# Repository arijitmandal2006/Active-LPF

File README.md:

**Active Low-Pass Filter (Sallen--Key) Using TLV9061**
=====================================================

### *Designed by Arijit Mandal*

This repository contains the full KiCad project, schematic, PCB design, and supporting documentation for a **2nd-order active low-pass filter** based on the **TLV9061** high-performance CMOS op-amp.\
The filter is implemented in a **unity-gain Sallen--Key topology**, optimized for clean analog signal conditioning.

* * * * *

📘 **Project Overview**
-----------------------

This project implements a precision **Active Low Pass Filter (LPF)** suitable for:

-   Sensor signal conditioning

-   Noise filtering in embedded electronics

-   General analog experimentation

The LPF is centered around the **TLV9061**, a modern rail-to-rail, low-noise, high-bandwidth CMOS operational amplifier from Texas Instruments.

A complete KiCad schematic is shown in **page 1 of the submitted schematic PDF**
**Filter Characteristics**
--------------------------

-   **Topology:**  2nd Order

-   **Configuration:** Unity-gain

-   **Cutoff Frequency (fc):** ~1 kHz (based on selected RC values)

-   **Supply Options:**

    -   **Single-Supply:** +5 V

    -   **Dual-Supply:** +5 V / --5 V

-   **Input Type:** Single-ended AC input

-   **Output Type:** Buffered, low-impedance analog output

* * * * *

📐 **Circuit Diagram**
----------------------
The circuit schematic includes:

-   A AC test source

-   RC network (R1, R2, C1, C2) 

-   TLV9061 op-amp with VCC, VEE, and ground

-   Input/output connectors

-   Proper PWR_FLAG usage for clean KiCad ERC.

| Component | Value | Footprint | Notes |
| --- | --- | --- | --- |
| **R1** | 13 kΩ | Axial | Forms RC time constant |
| **R2** | 9.53 kΩ | Axial | Improves Q factor |
| **C1** | 20.5 nF | Axial / radial  | Feedback capacitor |
| **C2** | 10 nF | Axial  | Shunt-to-ground capacitor |
| **U1** | **TLV9061** | SOT-23-5 | Rail-to-rail precision op-amp |
| **Connectors** | VIN / VCC / VEE / OUT | Pin Header 2.54 mm | For easy prototyping |
---------------------------------
⚡ **TLV9061 --- Key Specifications**
----------------------------------

**General**

-   Single-channel CMOS op-amp

-   Rail-to-rail input and output

-   Supply range: **1.8 V to 5.5 V** (single-supply)

-   Slew rate: **6.5 V/µs**

-   Gain bandwidth (GBW): **10 MHz**

-   Noise: **10.5 nV/√Hz** at 1 kHz

**Electrical**

-   Input offset voltage: **±150 µV (typ.)**

-   Output current: **±75 mA**

-   Input bias current: **±1 pA (typ.)**

-   Quiescent current: **180 µA (typ.)**

**Why TLV9061 is ideal for this LPF:**

-   High-speed and low-noise response improves filter accuracy

-   Rail-to-rail I/O supports low-voltage operation

-   Stable in unity-gain configuration (critical for Sallen--Key)

-   Small SOT-23-5 package suits compact analog boards
-   
----------------------------------------
🚀 **How to Use the Board**
---------------------------

### 1\. **Power the Board**

Choose one of:

-   **Single supply:**

    `VCC = +5 V
    VEE = GND`

-   **Dual supply:**

    `VCC = +5 V
    VEE = --5 V`

### 2\. **Connect Input Signal**

Use the VIN header:

`Signal → VIN
Ground → GND`

### 3\. **Read the Filtered Output**

Use the OUT header:

`Filtered signal → OUT
Return → GND`
----------------------

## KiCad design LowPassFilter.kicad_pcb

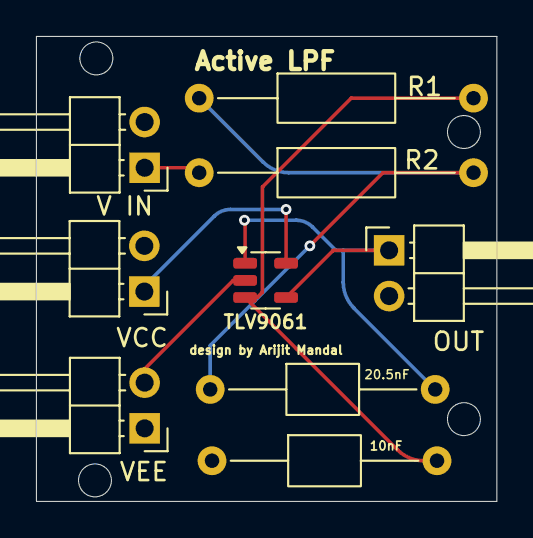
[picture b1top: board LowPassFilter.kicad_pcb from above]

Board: 2 copper layers, 25.6 x 25.8 mm, 9 parts (0 on the bottom side), 7 nets.

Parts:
10nF: 10n; C_Axial_L3.8mm_D2.6mm_P12.50mm_Horizontal
20.5nF: 20.5n; C_Axial_L3.8mm_D2.6mm_P12.50mm_Horizontal
OUT: OUT; PinHeader_1x02_P2.54mm_Horizontal
R1: 13k; R_Axial_DIN0207_L6.3mm_D2.5mm_P15.24mm_Horizontal
R2: 9.53k; R_Axial_DIN0207_L6.3mm_D2.5mm_P15.24mm_Horizontal
TLV9061: TLV9061; SOT-23-5
V IN: VSIN; PinHeader_1x02_P2.54mm_Horizontal
VCC: 5; PinHeader_1x02_P2.54mm_Horizontal
VEE: 5; PinHeader_1x02_P2.54mm_Horizontal

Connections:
GND: 10nF.1, OUT.2, V IN.2, VCC.2, VEE.1
unnamed: 20.5nF.1, R1.1, R2.2
unnamed: 10nF.2, R1.2, TLV9061.3 (+)
VCC: TLV9061.5 (V+), VCC.1
VEE: TLV9061.2 (V-), VEE.2
in: R2.1, V IN.1
out: 20.5nF.2, OUT.1, TLV9061.1, TLV9061.4 (-)

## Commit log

2025-11-30 Add README for Active Low-Pass Filter project
    Added detailed documentation for the Active Low-Pass Filter project, including project overview, filter characteristics, circuit diagram, component specifications, and usage instructions.
